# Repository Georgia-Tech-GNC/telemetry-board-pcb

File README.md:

# KiCad Project Template
Copy this template to quickly start a new KiCad project.

## Setup Steps
1. Copy template
2. SOME STUFF
3. Add libraries to project library table

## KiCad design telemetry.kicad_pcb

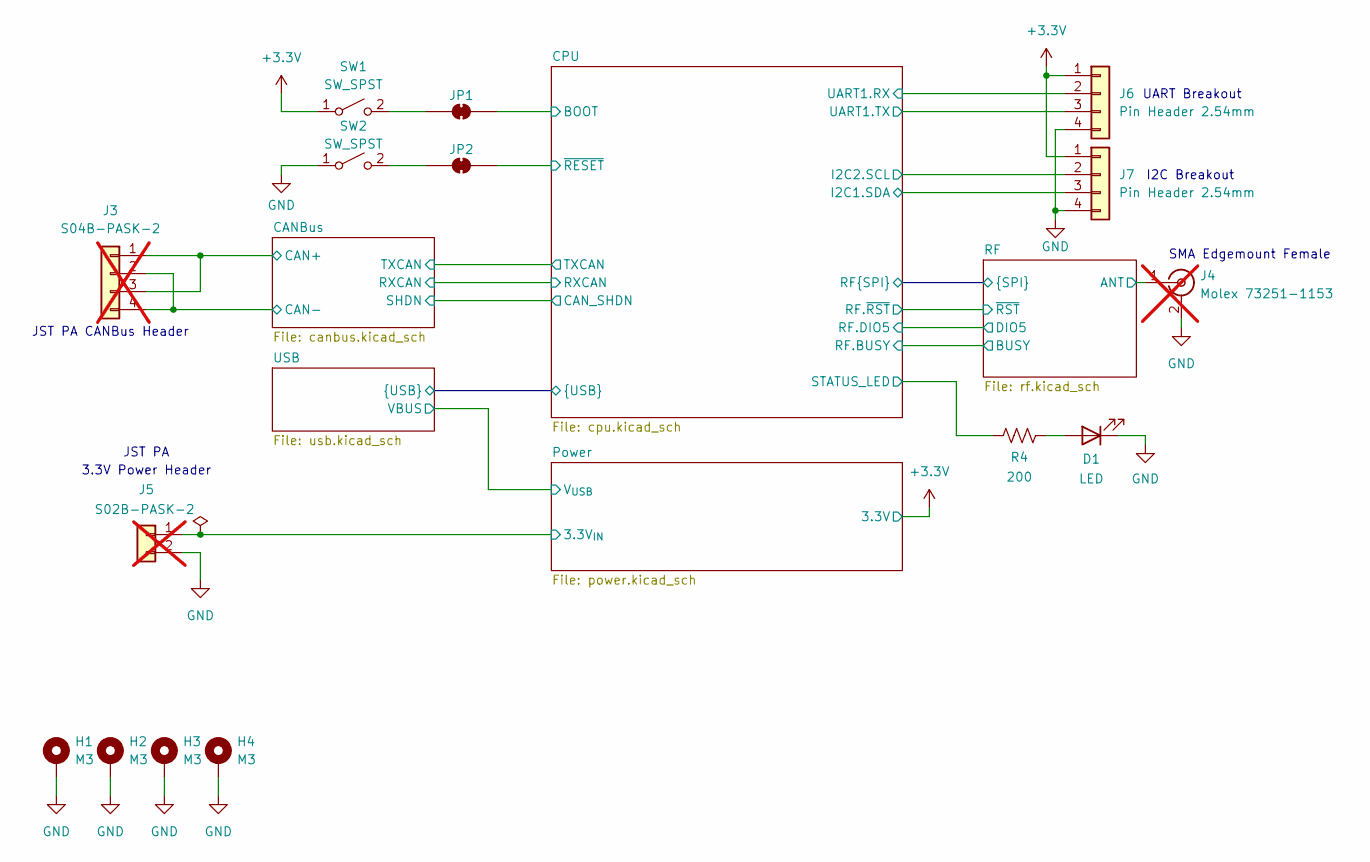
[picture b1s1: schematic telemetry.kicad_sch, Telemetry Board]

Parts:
D1: LED; LED_0603_1608Metric; MPN KT-0603R; LCSC C2286
H1, H2, H3, H4: M3; MountingHole_3.2mm_M3_Pad
J3: S04B-PASK-2; JST_S04B-PASK-2_LF__SN_; MPN S04B-PASK-2; Digikey 455-S04B-PASK-2-ND; not fitted
J4: Molex 73251-1153; SMA_Molex_73251-1153_EdgeMount_Horizontal; MPN 732511150; LCSC C841205; not fitted
J5: S02B-PASK-2; JST_S02B-PASK-2; MPN S02B-PASK-2; Digikey 455-S02B-PASK-2-ND; not fitted
J6, J7: Pin Header 2.54mm; PinHeader_1x04_P2.54mm_Vertical
JP1, JP2: SolderJumper_2_Bridged; SolderJumper-2_P1.3mm_Bridged_RoundedPad1.0x1.5mm
R4: 200; R_0805_2012Metric; MPN 0805W8F2000T5E; LCSC C17540
SW1, SW2: SW_SPST; SW_SPST_PTS647_Sx38; MPN PTS 647 SN38 SMTR2 LFS; LCSC C2799279

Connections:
+3.3V: J6.1, J7.1, SW1.1 (A); also elsewhere on the board
/CANBus/CAN+: J3.1, J3.3; also elsewhere on the board
/CANBus/CAN-: J3.2, J3.4; also elsewhere on the board
/CPU/BOOT: JP1.2 (B); also elsewhere on the board
/CPU/I2C1.SDA: J7.3; also elsewhere on the board
/CPU/I2C2.SCL: J7.2; also elsewhere on the board
/CPU/STATUS_LED: R4.1; also elsewhere on the board
/CPU/UART1.RX: J6.2; also elsewhere on the board
/CPU/UART1.TX: J6.3; also elsewhere on the board
/CPU/~RESET: JP2.2 (B); also elsewhere on the board
/Power/3.3V_{IN}: J5.1; also elsewhere on the board
/RF/ANT: J4.1 (In); also elsewhere on the board
GND: D1.1 (K), H1.1 (1_1), H2.1 (1_1), H3.1 (1_1), H4.1 (1_1), J4.2 (Ext), J5.2, J6.4, J7.4, SW2.1 (A); also elsewhere on the board
unnamed: D1.2 (A), R4.2
unnamed: JP1.1 (A), SW1.2 (B)
unnamed: JP2.1 (A), SW2.2 (B)

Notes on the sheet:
I2C Breakout
JST PA CANBus Header
3.3V Power Header
UART Breakout
SMA Edgemount Female
JST PA

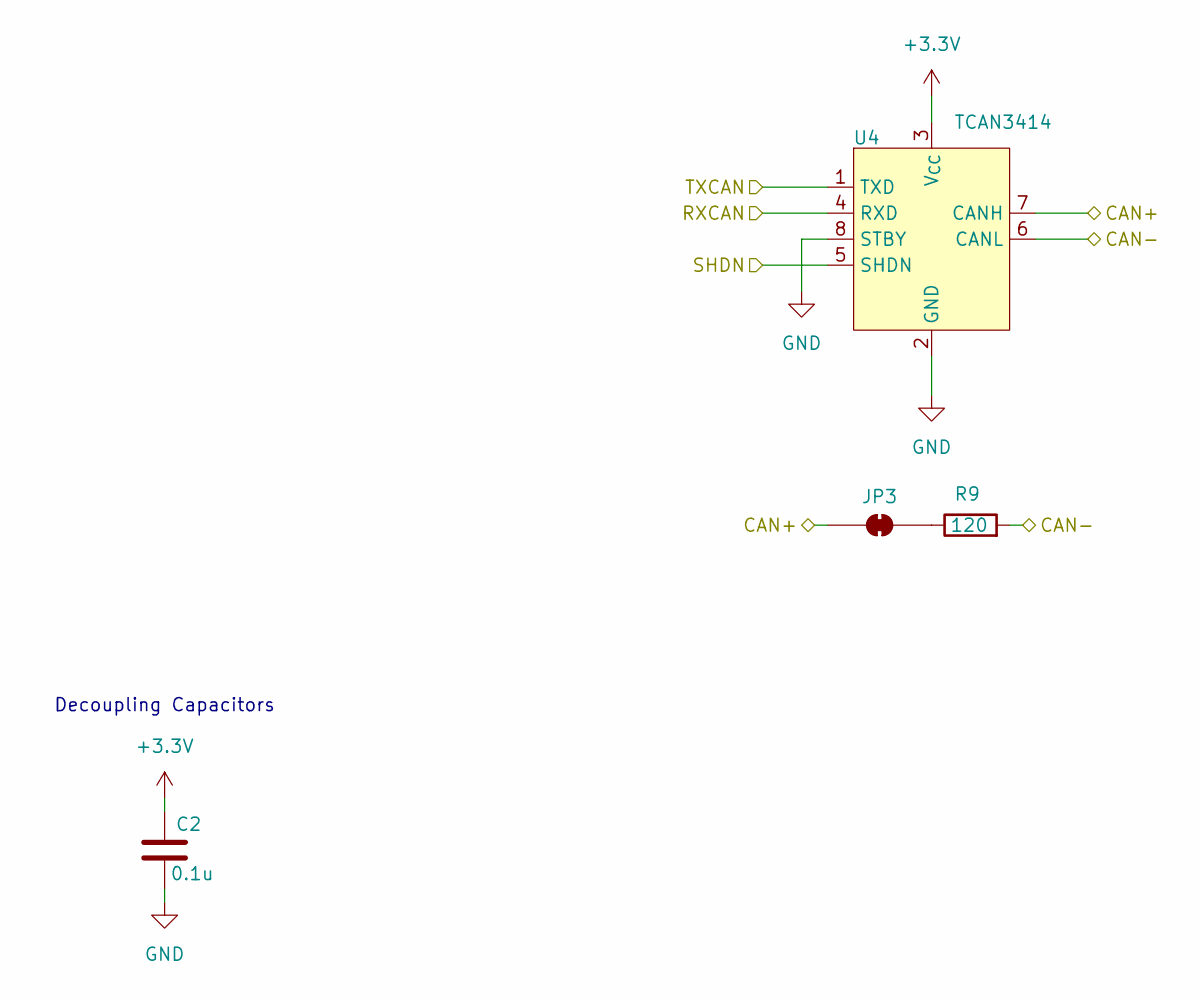
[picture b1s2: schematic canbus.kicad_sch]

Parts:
C2: 0.1u; C_0402_1005Metric; MPN CL05B104KO5NNNC; Digikey 1276-1003-1-ND
JP3: SolderJumper_2_Bridged; SolderJumper-2_P1.3mm_Bridged_RoundedPad1.0x1.5mm
R9: 120; R_0805_2012Metric; MPN 0805W8F1200T5E; LCSC C17437
U4: TCAN3414; SOIC-8_3.9x4.9mm_P1.27mm; MPN TCAN3413DR; LCSC C22433320

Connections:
+3.3V: C2.1, U4.3 (V_{CC}); also elsewhere on the board
/CANBus/CAN+: JP3.1 (A), U4.7 (CANH); also elsewhere on the board
/CANBus/CAN-: R9.2, U4.6 (CANL); also elsewhere on the board
/CANBus/RXCAN: U4.4 (RXD); also elsewhere on the board
/CANBus/SHDN: U4.5 (SHDN); also elsewhere on the board
/CANBus/TXCAN: U4.1 (TXD); also elsewhere on the board
GND: C2.2, U4.2 (GND), U4.8 (STBY); also elsewhere on the board
unnamed: JP3.2 (B), R9.1

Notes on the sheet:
Decoupling Capacitors

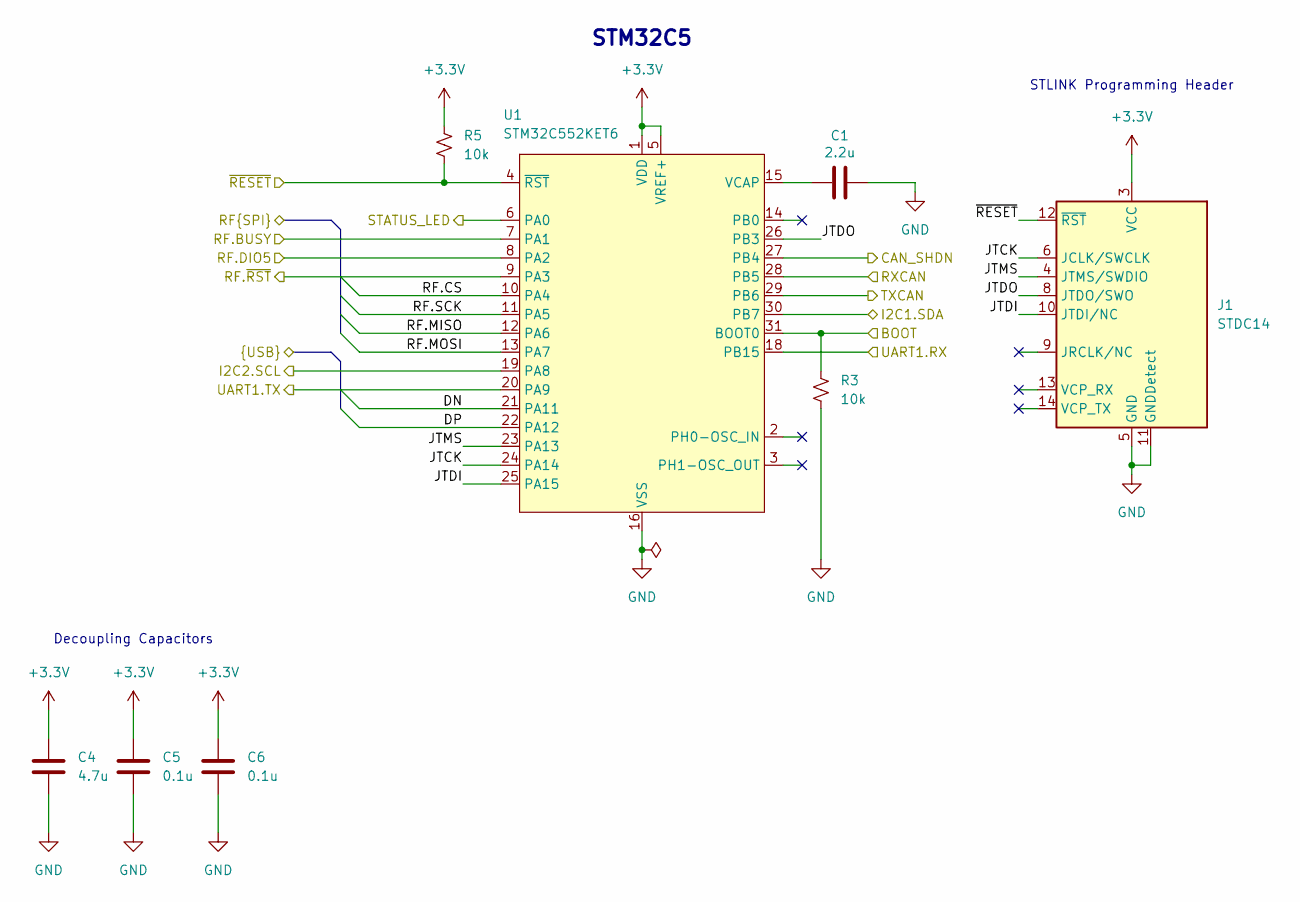
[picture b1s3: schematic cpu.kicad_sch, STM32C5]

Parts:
C1: 2.2u; C_0402_1005Metric; MPN CL05A225MQ5NSNC; LCSC C12530
C4: 4.7u; C_1206_3216Metric; MPN CL31B475KBHNNNE; LCSC C51205
C5, C6: 0.1u; C_0402_1005Metric; MPN CL05B104KO5NNNC; Digikey 1276-1003-1-ND
J1: STDC14; SAMTEC_FTSH-107-01-L-DV-K-A; MPN FTSH-107-01-L-DV-K-A; LCSC C5563894
R3, R5: 10k; R_0805_2012Metric; MPN 0805W8F1002T5E; LCSC C17414
U1: STM32C552KET6; LQFP-32_7x7mm_P0.8mm; MPN STM32C552KET6; Digikey 497-STM32C552KET6-ND

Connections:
+3.3V: C4.1, C5.1, C6.1, J1.3 (VCC), R5.1, U1.1 (VDD), U1.5 (VREF+), U1.17 (VDD); also elsewhere on the board
/CANBus/RXCAN: U1.28 (PB5); also elsewhere on the board
/CANBus/SHDN: U1.27 (PB4); also elsewhere on the board
/CANBus/TXCAN: U1.29 (PB6); also elsewhere on the board
/CPU/BOOT: R3.1, U1.31 (BOOT0); also elsewhere on the board
/CPU/DN: U1.21 (PA11); also elsewhere on the board
/CPU/DP: U1.22 (PA12); also elsewhere on the board
/CPU/I2C1.SDA: U1.30 (PB7); also elsewhere on the board
/CPU/I2C2.SCL: U1.19 (PA8); also elsewhere on the board
/CPU/JTCK: J1.6 (JCLK/SWCLK), U1.24 (PA14)
/CPU/JTDI: J1.10 (JTDI/NC), U1.25 (PA15)
/CPU/JTDO: J1.8 (JTDO/SWO), U1.26 (PB3)
/CPU/JTMS: J1.4 (JTMS/SWDIO), U1.23 (PA13)
/CPU/RF.BUSY: U1.7 (PA1); also elsewhere on the board
/CPU/RF.CS: U1.10 (PA4); also elsewhere on the board
/CPU/RF.DIO5: U1.8 (PA2); also elsewhere on the board
/CPU/RF.MISO: U1.12 (PA6); also elsewhere on the board
/CPU/RF.MOSI: U1.13 (PA7); also elsewhere on the board
/CPU/RF.SCK: U1.11 (PA5); also elsewhere on the board
/CPU/RF.~RST: U1.9 (PA3); also elsewhere on the board
/CPU/STATUS_LED: U1.6 (PA0); also elsewhere on the board
/CPU/UART1.RX: U1.18 (PB15); also elsewhere on the board
/CPU/UART1.TX: U1.20 (PA9); also elsewhere on the board
/CPU/~RESET: J1.12 (~RST), R5.2, U1.4 (~RST); also elsewhere on the board
GND: C1.2, C4.2, C5.2, C6.2, J1.5 (GND), J1.7 (GND), J1.11 (GNDDetect), R3.2, U1.16 (VSS), U1.32 (VSS); also elsewhere on the board
unnamed: C1.1, U1.15 (VCAP)

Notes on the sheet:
STLINK Programming Header
Decoupling Capacitors
STM32C5

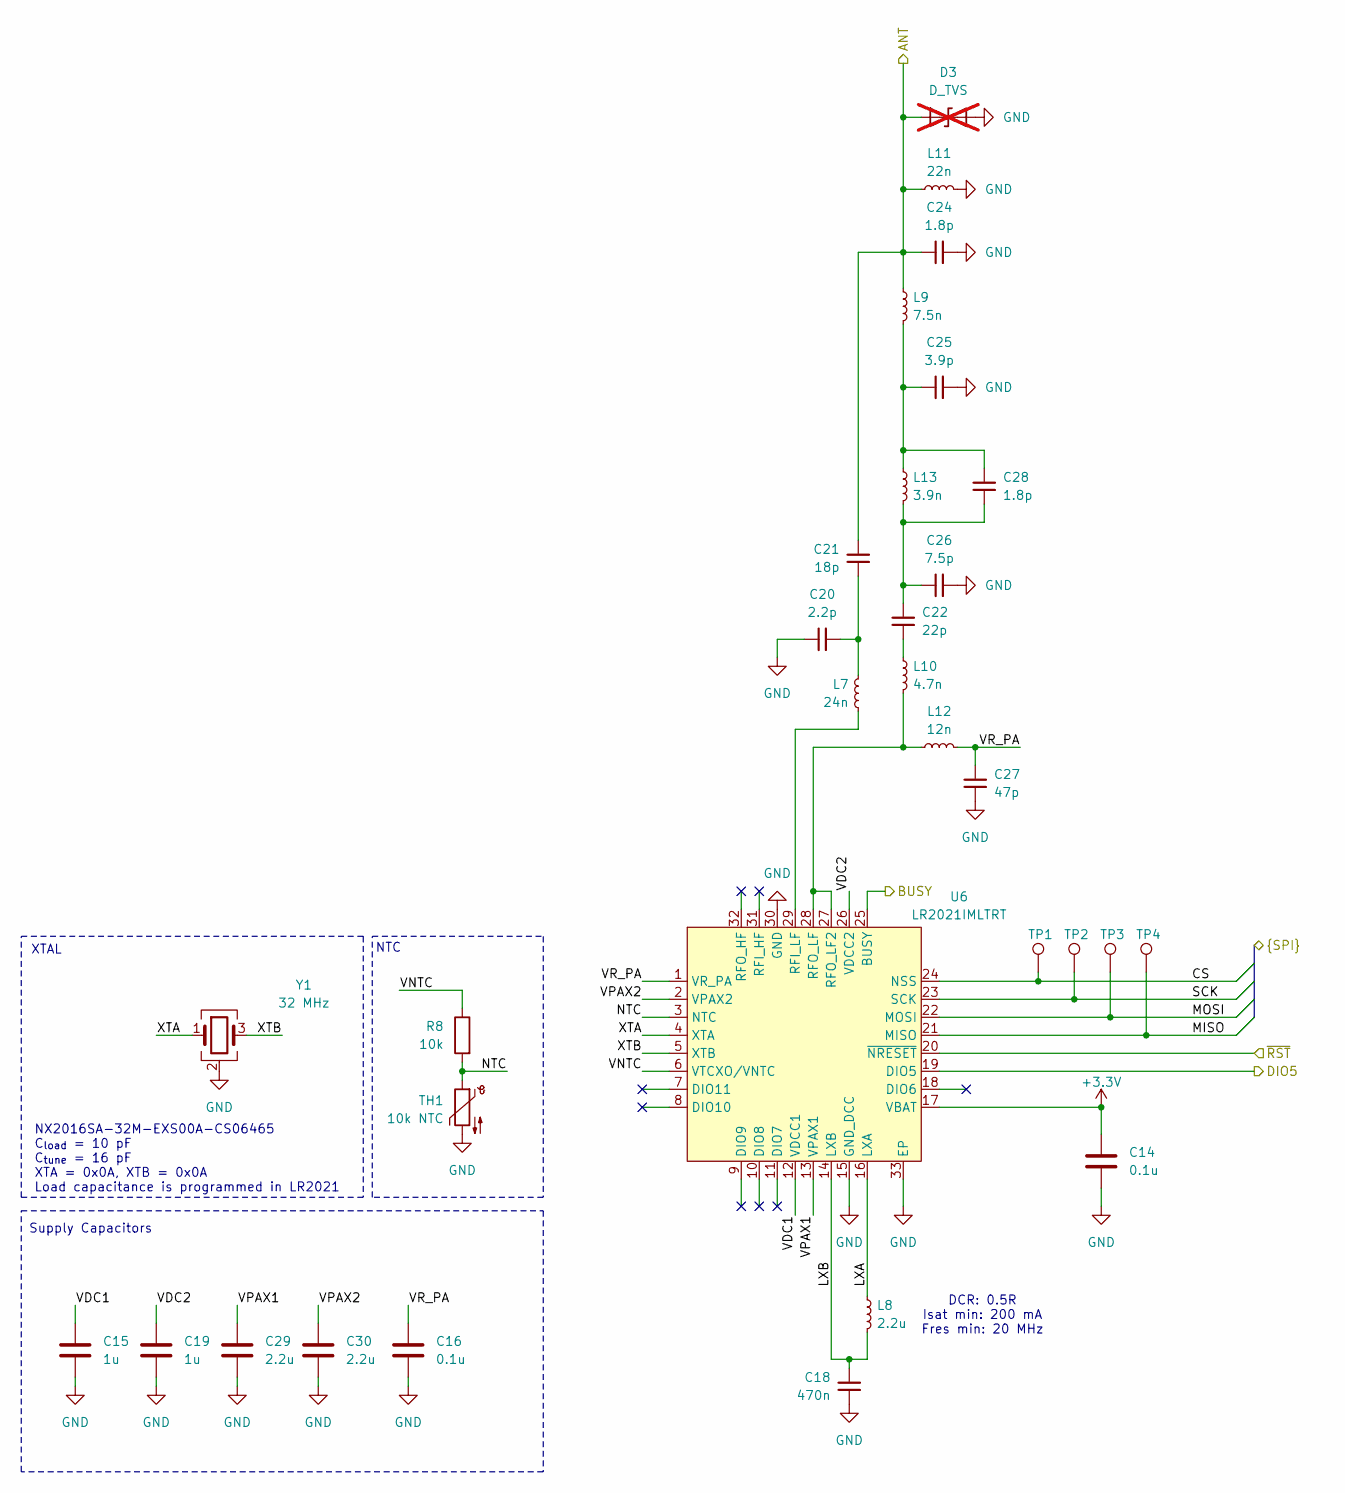
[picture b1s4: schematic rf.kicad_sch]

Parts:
C14: 0.1u; C_0402_1005Metric; MPN CL05B104KO5NNNC; Digikey 1276-1003-1-ND
C15, C19: 1u; C_0402_1005Metric; MPN CL05A105KO5NNNC; LCSC C29266
C16: 0.1u; C_0402_1005Metric; MPN CL05B104KO5NNNC; LCSC C1525
C18: 470n; C_0402_1005Metric; MPN CL05A474KP5NNNC; LCSC C47339
C20: 2.2p; C_0402_1005Metric; MPN 0402CG2R2C500NT; LCSC C1559
C21: 18p; C_0402_1005Metric; MPN 0402CG180J500NT; LCSC C1549
C22: 22p; C_0402_1005Metric; MPN 0402CG220J500NT; LCSC C1555
C24, C28: 1.8p; C_0402_1005Metric; MPN 0402CG1R8C500NT; LCSC C1553
C25: 3.9p; C_0402_1005Metric; MPN 0402CG3R9C500NT; LCSC C1566
C26: 7.5p; C_0402_1005Metric; MPN 0402CG7R5C500NT; LCSC C43514
C27: 47p; C_0402_1005Metric; MPN 0402CG470J500NT; LCSC C1567
C29, C30: 2.2u; C_0402_1005Metric; MPN CL05A225MQ5NSNC; LCSC C12530
D3: D_TVS; D_0402_1005Metric; not fitted
L7: 24n; L_0402_1005Metric; MPN LQW15AN24NG80D; LCSC C668462
L8: 2.2u; L_0805_2012Metric; MPN CMI201209U2R2KT; LCSC C1043
L9: 7.5n; L_0402_1005Metric; MPN LQW15AN7N5G00D; LCSC C82918
L10: 4.7n; L_0402_1005Metric; MPN LQG15HS4N7B02D; LCSC C162543
L11: 22n; L_0402_1005Metric; MPN LQW15AN22NG00D; LCSC C86129
L12: 12n; L_0402_1005Metric; MPN LQW15AN12NG80D; LCSC C3223181
L13: 3.9n; L_0402_1005Metric; MPN SDCL1005C3N9STDF; LCSC C14033
R8: 10k; R_0402_1005Metric; MPN 0402WGF1002TCE; LCSC C25744
TH1: 10k NTC; R_0402_1005Metric; MPN NTCG103JF103FT1S; LCSC C5121989
TP1, TP2, TP3, TP4: TestPoint; TestPoint_Pad_D1.5mm
U6: LR2021IMLTRT; QFN-32-1EP_5x5mm_P0.5mm_EP3.7x3.7mm; MPN LR2021IMLTRT; LCSC C49421489
Y1: 32 MHz; Crystal_SMD_2016-4Pin_2.0x1.6mm; MPN NX2016SA-32M-EXS00A-CS06465; LCSC C1986260

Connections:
+3.3V: C14.1, U6.17 (VBAT); also elsewhere on the board
/CPU/RF.BUSY: U6.25 (BUSY); also elsewhere on the board
/CPU/RF.CS: TP1.1 (1_1), U6.24 (NSS); also elsewhere on the board
/CPU/RF.DIO5: U6.19 (DIO5); also elsewhere on the board
/CPU/RF.MISO: TP4.1 (1_1), U6.21 (MISO); also elsewhere on the board
/CPU/RF.MOSI: TP3.1 (1_1), U6.22 (MOSI); also elsewhere on the board
/CPU/RF.SCK: TP2.1 (1_1), U6.23 (SCK); also elsewhere on the board
/CPU/RF.~RST: U6.20 (~NRESET); also elsewhere on the board
/RF/ANT: C21.2, C24.1, D3.1 (A1), L9.1, L11.1; also elsewhere on the board
/RF/LXA: L8.1, U6.16 (LXA)
/RF/LXB: C18.1, L8.2, U6.14 (LXB)
/RF/NTC: R8.2, TH1.1, U6.3 (NTC)
/RF/VDC1: C15.1, U6.12 (VDCC1)
/RF/VDC2: C19.1, U6.26 (VDCC2)
/RF/VNTC: R8.1, U6.6 (VTCXO/VNTC)
/RF/VPAX1: C29.1, U6.13 (VPAX1)
/RF/VPAX2: C30.1, U6.2 (VPAX2)
/RF/VR_PA: C16.1, C27.1, L12.2, U6.1 (VR_PA)
/RF/XTA: U6.4 (XTA), Y1.1
/RF/XTB: U6.5 (XTB), Y1.3
GND: C14.2, C15.2, C16.2, C18.2, C19.2, C20.1, C24.2, C25.2, C26.2, C27.2, C29.2, C30.2, D3.2 (A2), L11.2, TH1.2, U6.15 (GND_DCC), U6.30 (GND), U6.33 (EP), Y1.2 (G), Y1.4 (G); also elsewhere on the board
unnamed: C20.2, C21.1, L7.1
unnamed: C22.1, L10.1
unnamed: C22.2, C26.1, C28.1, L13.2
unnamed: C25.1, C28.2, L9.2, L13.1
unnamed: L7.2, U6.29 (RFI_LF)
unnamed: L10.2, L12.1, U6.27 (RFO_LF2), U6.28 (RFO_LF)

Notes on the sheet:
Supply Capacitors
XTAL
DCR: 0.5R Isat min: 200 mA Fres min: 20 MHz
NX2016SA-32M-EXS00A-CS06465 C_{load} = 10 pF C_{tune} = 16 pF XTA = 0x0A, XTB = 0x0A Load capacitance is programmed in LR2021
NTC

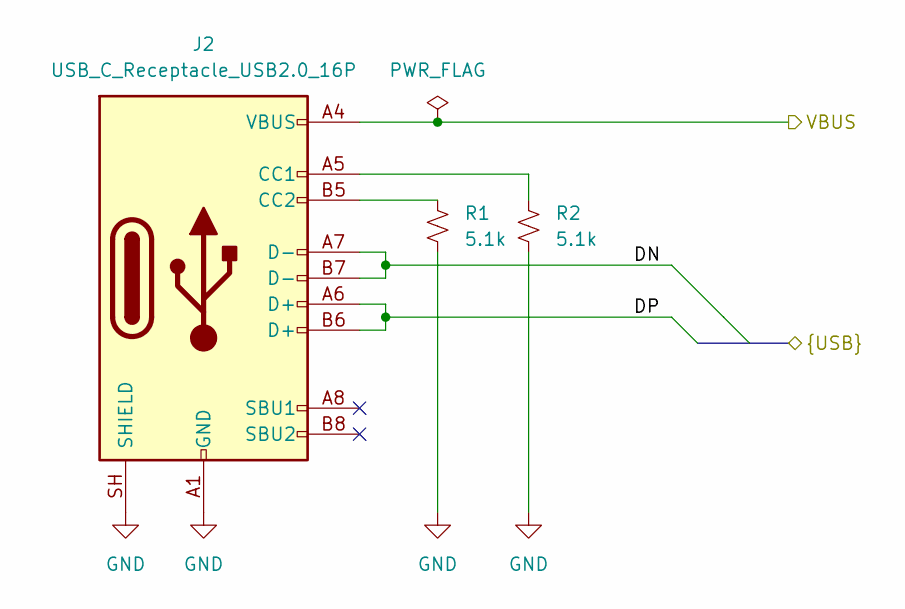
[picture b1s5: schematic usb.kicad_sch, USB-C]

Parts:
J2: USB_C_Receptacle_USB2.0_16P; AMPHENOL_12402012E212A; MPN GT-USB-9010A; Digikey 664-12402012E212ACT-ND
R1, R2: 5.1k; R_0805_2012Metric; MPN 0805W8F5101T5E; LCSC C27834

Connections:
/CPU/DN: J2.A7 (D-), J2.B7 (D-); also elsewhere on the board
/CPU/DP: J2.A6 (D+), J2.B6 (D+); also elsewhere on the board
/Power/V_{USB}: J2.A4 (VBUS), J2.A9 (VBUS), J2.B4 (VBUS), J2.B9 (VBUS); also elsewhere on the board
GND: J2.A1 (GND), J2.A12 (GND), J2.B1 (GND), J2.B12 (GND), J2.SH (SHIELD), R1.2, R2.2; also elsewhere on the board
unnamed: J2.A5 (CC1), R2.1
unnamed: J2.B5 (CC2), R1.1

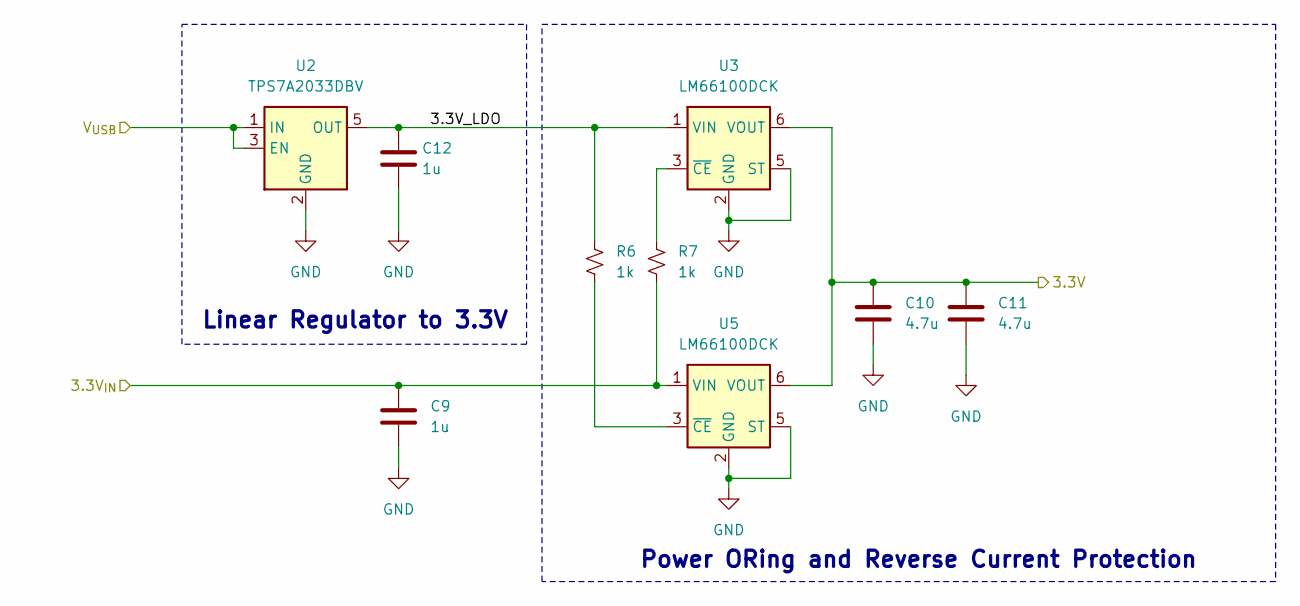
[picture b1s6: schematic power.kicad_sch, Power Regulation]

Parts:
C9, C12: 1u; C_0402_1005Metric; MPN CL05A105KO5NNNC; LCSC C29266
C10, C11: 4.7u; C_1206_3216Metric; MPN CL31B475KBHNNNE; LCSC C51205
R6, R7: 1k; R_0805_2012Metric; MPN 0805W8F1001T5E; LCSC C17513
U2: TPS7A2033DBV; SOT-23-5; MPN TPS7A2033PDBVR; LCSC C2862740
U3, U5: LM66100DCK; SOT-363_SC-70-6; MPN LM66100DCKR; LCSC C2869734

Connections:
+3.3V: C10.1, C11.1, U3.6 (VOUT), U5.6 (VOUT); also elsewhere on the board
/Power/3.3V_LDO: C12.1, R6.1, U2.5 (OUT), U3.1 (VIN)
/Power/3.3V_{IN}: C9.1, R7.2, U5.1 (VIN); also elsewhere on the board
/Power/V_{USB}: U2.1 (IN), U2.3 (EN); also elsewhere on the board
GND: C9.2, C10.2, C11.2, C12.2, U2.2 (GND), U3.2 (GND), U3.5 (ST), U5.2 (GND), U5.5 (ST); also elsewhere on the board
unnamed: R7.1, U3.3 (~CE)
unnamed: R6.2, U5.3 (~CE)

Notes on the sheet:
Linear Regulator to 3.3V
Power ORing and Reverse Current Protection

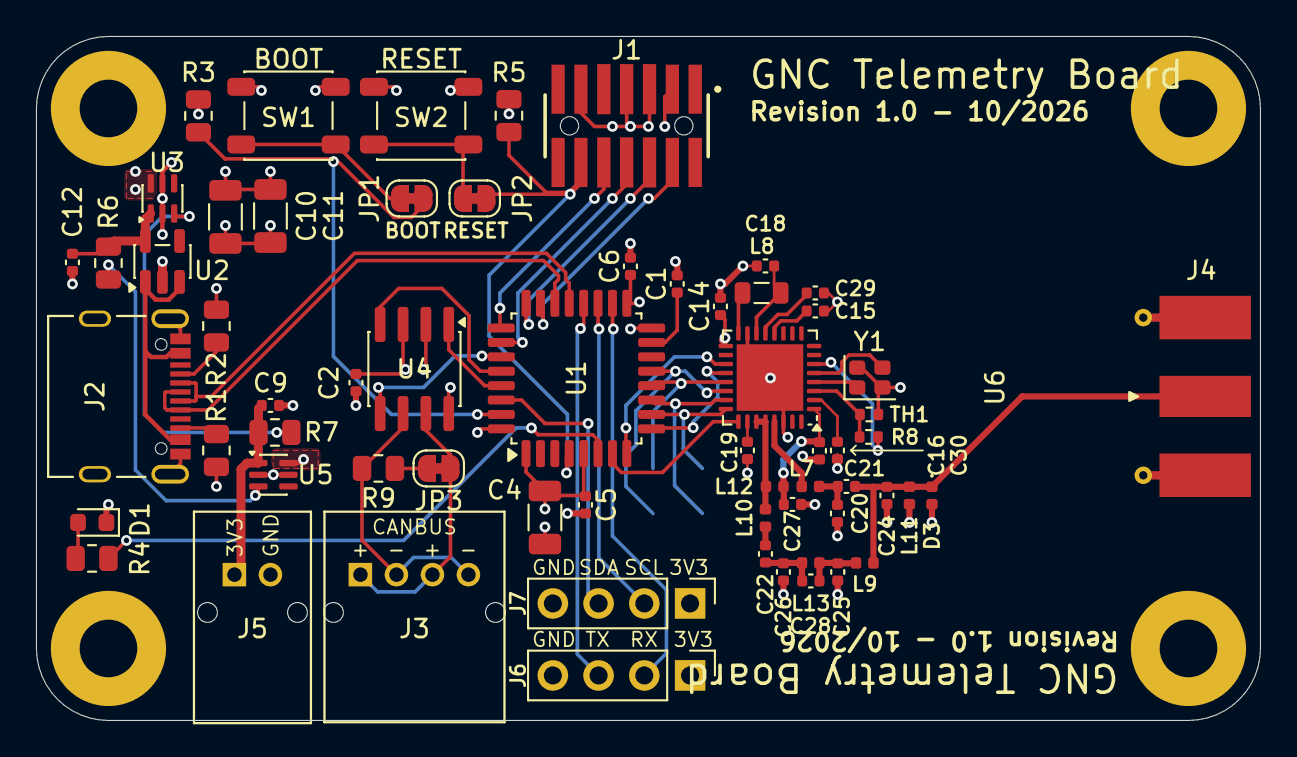
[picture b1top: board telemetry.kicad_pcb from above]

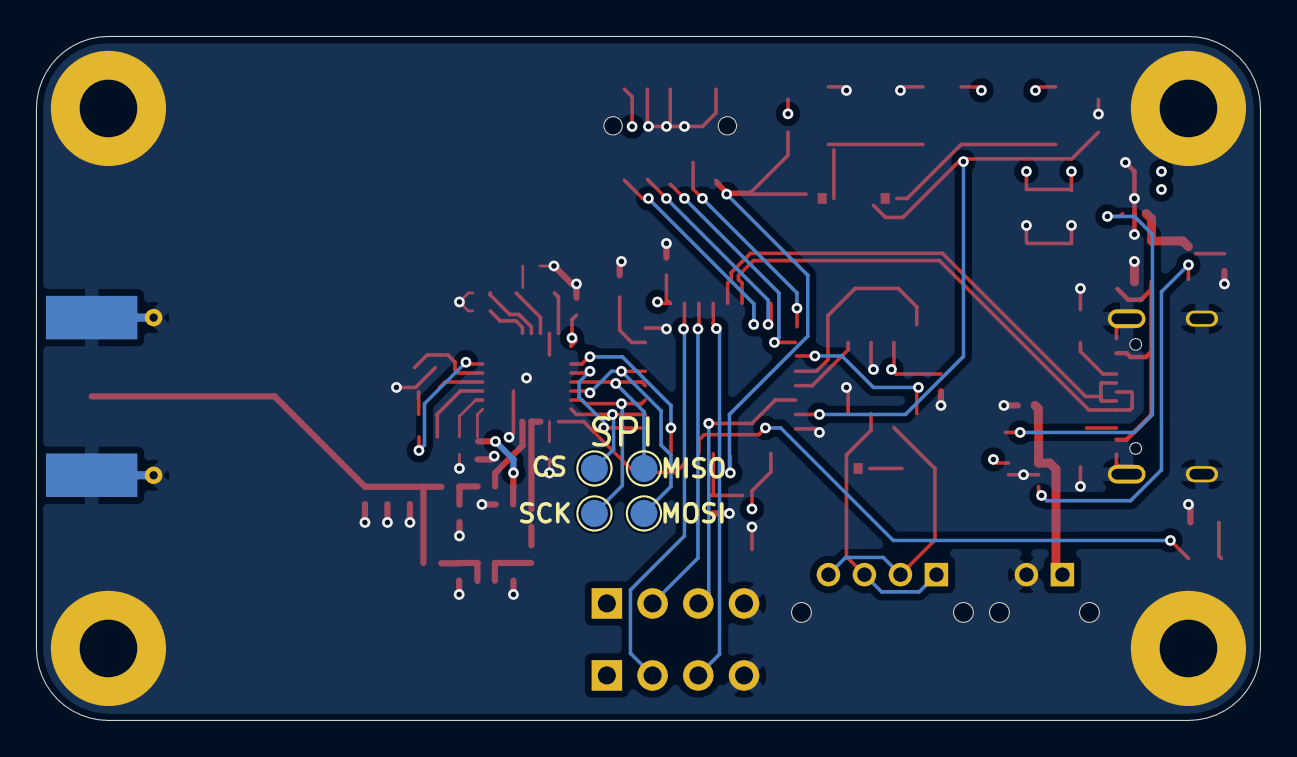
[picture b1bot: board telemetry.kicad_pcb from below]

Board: 4 copper layers, 68.0 x 38.0 mm, 70 parts (4 on the bottom side), 57 nets.
